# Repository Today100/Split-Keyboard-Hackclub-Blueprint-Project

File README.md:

# Split-Keyboard-Hackclub-Blueprint-Project
A split keyboard using the Seeed Studio XIAO nRF52840. Inspired by my dad, who likes looking at different kinds of keyboards. I'd like to make one to practice my skills in hardware design and give it to him as a gift. It has a Bluetooth feature and is rechargeable.

### Overview

|Part|Image|
|---|---|
|Full Product||
|Case||
|PCB||
|Schematics||

### BOM
BOM.csv is available for review

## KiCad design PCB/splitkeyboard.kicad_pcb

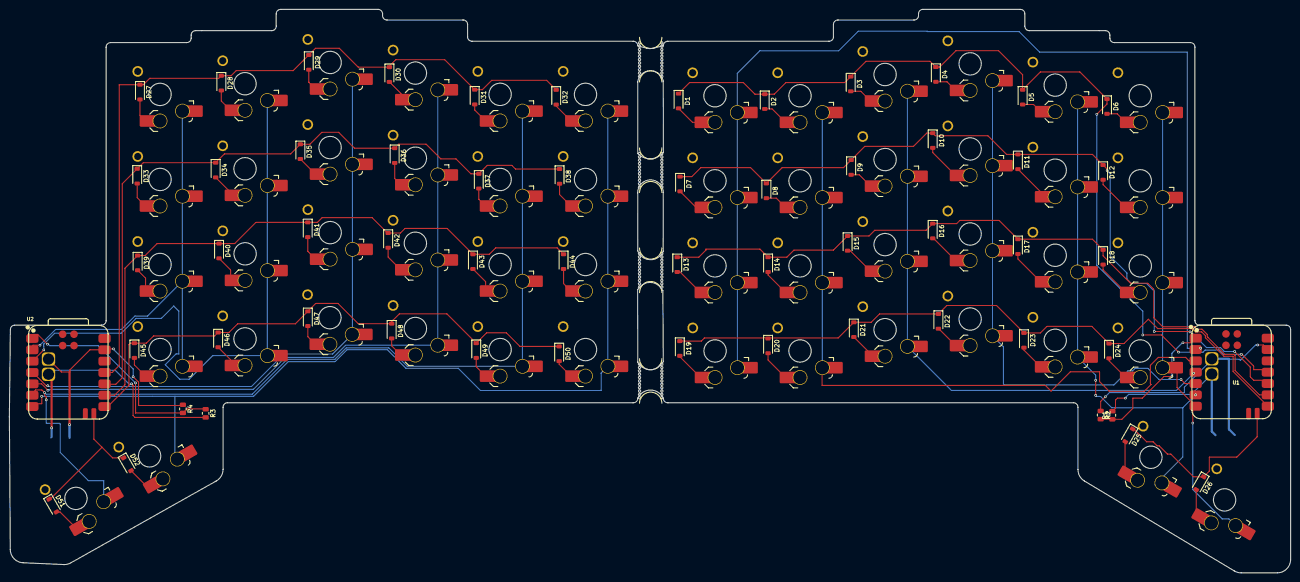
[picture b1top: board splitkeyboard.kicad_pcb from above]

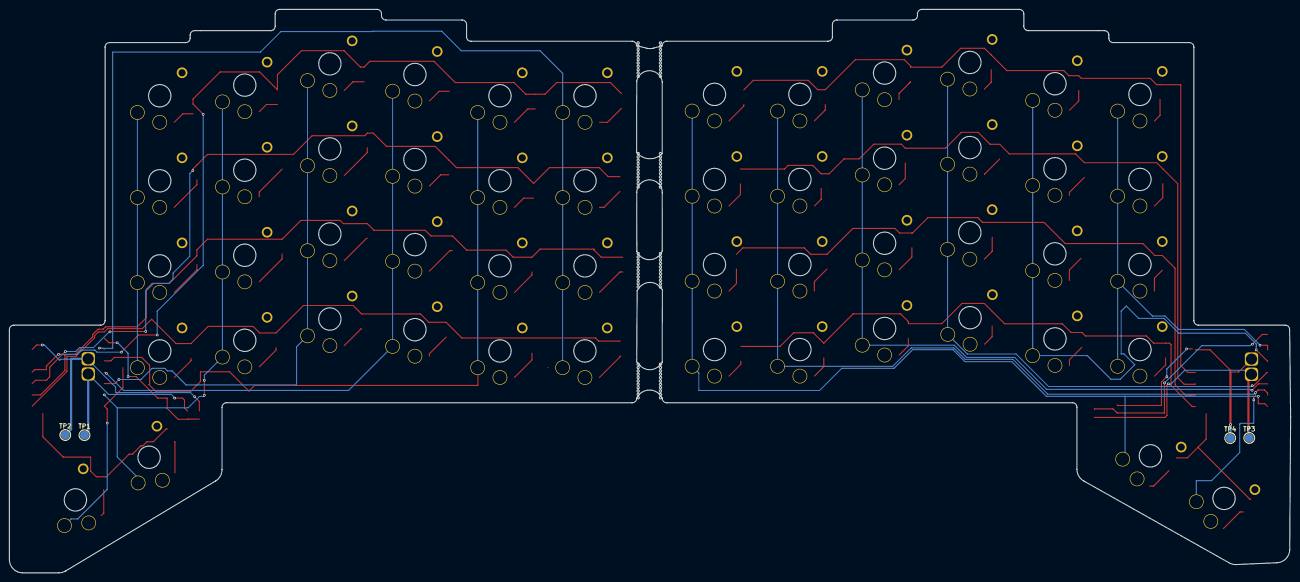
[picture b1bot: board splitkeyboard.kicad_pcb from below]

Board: 2 copper layers, 287.0 x 126.2 mm, 118 parts (4 on the bottom side), 79 nets.

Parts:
D1, D2, D3, D4, D5, D6, D7, D8, D9, D10, D11, D12, D13, D14, D15, D16, D17, D18, D19, D20, D21, D22, D23, D24, D25, D26, D27, D28, D29, D30, D31, D32, D33, D34, D35, D36, D37, D38, D39, D40, D41, D42, D43, D44, D45, D46, D47, D48, D49, D50, D51, D52: D; D_SOD-123
H1, H3, H4, H5: MountingHole; mouse-bite-5mm-slot
R1, R3: 806k; R_0805_2012Metric
R2, R4: 2M; R_0805_2012Metric
SW1, SW2, SW3, SW4, SW5, SW6, SW7, SW8, SW9, SW10, SW11, SW12, SW13, SW14, SW15, SW16, SW17, SW18, SW19, SW20, SW21, SW22, SW23, SW24, SW25, SW26, SW27, SW28, SW29, SW30, SW31, SW32, SW33, SW34, SW35, SW36, SW37, SW38, SW39, SW40, SW41, SW42, SW43, SW44, SW45, SW46, SW47, SW48, SW49, SW50, SW51, SW52: SW_Push; SW_choc_v2_HS_CPG135001S30_1u
TP1, TP3: BAT; TestPoint_Pad_D2.0mm
TP2, TP4: GND; TestPoint_Pad_D2.0mm
U1, U2: XIAO-nRF52840-SMD; modified-XIAO-nRF52840-SMD

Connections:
/left/BT_PIN: R1.1, R2.2, U1.1 (P0.02_A0_D0)
/left/COL0: SW1.1, SW7.1, SW13.1, SW19.1, U1.2 (P0.03_A1_D1)
/left/COL1: SW2.1, SW8.1, SW14.1, SW20.1, U1.3 (P0.28_A2_D2)
/left/COL2: SW3.1, SW9.1, SW15.1, SW21.1, U1.4 (P0.29_A3_D3)
/left/COL3: SW4.1, SW10.1, SW16.1, SW22.1, U1.5 (P0.04_A4_D4_SDA)
/left/COL4: SW5.1, SW11.1, SW17.1, SW23.1, SW25.1, U1.6 (P0.05_A5_D5_SCL)
/left/COL5: SW6.1, SW12.1, SW18.1, SW24.1, SW26.1, U1.7 (P1.11_D6_TX)
/left/ROW0: D1.1 (K), D2.1 (K), D3.1 (K), D4.1 (K), D5.1 (K), D6.1 (K), U1.11 (P1.15_D10_MOSI)
/left/ROW1: D7.1 (K), D8.1 (K), D9.1 (K), D10.1 (K), D11.1 (K), D12.1 (K), U1.10 (P1.14_D9_MISO)
/left/ROW2: D13.1 (K), D14.1 (K), D15.1 (K), D16.1 (K), D17.1 (K), D18.1 (K), U1.9 (P1.13_D8_SCK)
/left/ROW3: D19.1 (K), D20.1 (K), D21.1 (K), D22.1 (K), D23.1 (K), D24.1 (K), U1.8 (P1.12_D7_RX)
/left/ROW4: D25.1 (K), D26.1 (K), U1.18 (NFC2)
/left/VBAT: R1.2, TP1.1, U1.15 (BAT)
/right/BT_PIN: R3.1, R4.2, U2.1 (P0.02_A0_D0)
/right/COL0: SW27.1, SW33.1, SW39.1, SW45.1, U2.2 (P0.03_A1_D1)
/right/COL1: SW28.1, SW34.1, SW40.1, SW46.1, U2.3 (P0.28_A2_D2)
/right/COL2: SW29.1, SW35.1, SW41.1, SW47.1, U2.4 (P0.29_A3_D3)
/right/COL3: SW30.1, SW36.1, SW42.1, SW48.1, U2.5 (P0.04_A4_D4_SDA)
/right/COL4: SW31.1, SW37.1, SW43.1, SW49.1, SW51.1, U2.6 (P0.05_A5_D5_SCL)
/right/COL5: SW32.1, SW38.1, SW44.1, SW50.1, SW52.1, U2.7 (P1.11_D6_TX)
/right/ROW0: D27.1 (K), D28.1 (K), D29.1 (K), D30.1 (K), D31.1 (K), D32.1 (K), U2.11 (P1.15_D10_MOSI)
/right/ROW1: D33.1 (K), D34.1 (K), D35.1 (K), D36.1 (K), D37.1 (K), D38.1 (K), U2.10 (P1.14_D9_MISO)
/right/ROW2: D39.1 (K), D40.1 (K), D41.1 (K), D42.1 (K), D43.1 (K), D44.1 (K), U2.9 (P1.13_D8_SCK)
/right/ROW3: D45.1 (K), D46.1 (K), D47.1 (K), D48.1 (K), D49.1 (K), D50.1 (K), U2.8 (P1.12_D7_RX)
/right/ROW4: D51.1 (K), D52.1 (K), U2.18 (NFC2)
/right/VBAT: R3.2, TP3.1, U2.15 (BAT)
GND: R2.1, R4.1, TP2.1, TP4.1, U1.13 (GND), U1.16 (GND), U2.13 (GND), U2.16 (GND)
unnamed: D1.2 (A), SW1.2
unnamed: D2.2 (A), SW2.2
unnamed: D3.2 (A), SW3.2
unnamed: D4.2 (A), SW4.2
unnamed: D5.2 (A), SW5.2
unnamed: D6.2 (A), SW6.2
unnamed: D7.2 (A), SW7.2
unnamed: D8.2 (A), SW8.2
unnamed: D9.2 (A), SW9.2
unnamed: D10.2 (A), SW10.2
unnamed: D11.2 (A), SW11.2
unnamed: D12.2 (A), SW12.2
unnamed: D13.2 (A), SW13.2
unnamed: D14.2 (A), SW14.2
unnamed: D15.2 (A), SW15.2
unnamed: D16.2 (A), SW16.2
unnamed: D17.2 (A), SW17.2
unnamed: D18.2 (A), SW18.2
unnamed: D19.2 (A), SW19.2
unnamed: D20.2 (A), SW20.2
unnamed: D21.2 (A), SW21.2
unnamed: D22.2 (A), SW22.2
unnamed: D23.2 (A), SW23.2
unnamed: D24.2 (A), SW24.2
unnamed: D25.2 (A), SW25.2
unnamed: D26.2 (A), SW26.2
unnamed: D27.2 (A), SW27.2
unnamed: D28.2 (A), SW28.2
unnamed: D29.2 (A), SW29.2
unnamed: D30.2 (A), SW30.2
unnamed: D31.2 (A), SW31.2
unnamed: D32.2 (A), SW32.2
unnamed: D33.2 (A), SW33.2
unnamed: D34.2 (A), SW34.2
unnamed: D35.2 (A), SW35.2
unnamed: D36.2 (A), SW36.2
unnamed: D37.2 (A), SW37.2
unnamed: D38.2 (A), SW38.2
unnamed: D39.2 (A), SW39.2
unnamed: D40.2 (A), SW40.2
unnamed: D41.2 (A), SW41.2
unnamed: D42.2 (A), SW42.2
unnamed: D43.2 (A), SW43.2
unnamed: D44.2 (A), SW44.2
unnamed: D45.2 (A), SW45.2
unnamed: D46.2 (A), SW46.2
unnamed: D47.2 (A), SW47.2
unnamed: D48.2 (A), SW48.2
unnamed: D49.2 (A), SW49.2
unnamed: D50.2 (A), SW50.2
unnamed: D51.2 (A), SW51.2
unnamed: D52.2 (A), SW52.2

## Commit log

2026-01-19 Create placeholder
2026-01-20 Remove placeholder file CAD/placeholder
2026-01-20 Remove placeholder content from Firmware/Placeholder
2026-01-20 Add BOM section to README
    Added a Bill of Materials (BOM) section with item details.
2026-01-20 Revise README with new components and pricing
    Updated component list with additional items and links, including diodes, resistors, and power switch.
2026-01-20 Fix total cost approximation in README
    Updated total cost approximation in the README.
2026-01-28 Revise BOM with updated pricing and sources
    Updated BOM section with detailed cost breakdown and links.
2026-01-28 Add product links and fix BOM formatting
    Updated BOM.csv to include product links and corrected formatting.
2026-01-28 Restore BOM.csv with updated item details
    Restored BOM.csv with updated item entries and prices.
2026-01-28 Enhance README with project details and images
    Added detailed project description and overview section with images.
2026-01-28 Update README with improved project description
    Revised project description for clarity and intent.
2026-02-07 Update BOM - Copy of Sheet1.csv with new entries
    Removed old data and added new BOM entries.
2026-02-07 Remove detailed BOM table from README
